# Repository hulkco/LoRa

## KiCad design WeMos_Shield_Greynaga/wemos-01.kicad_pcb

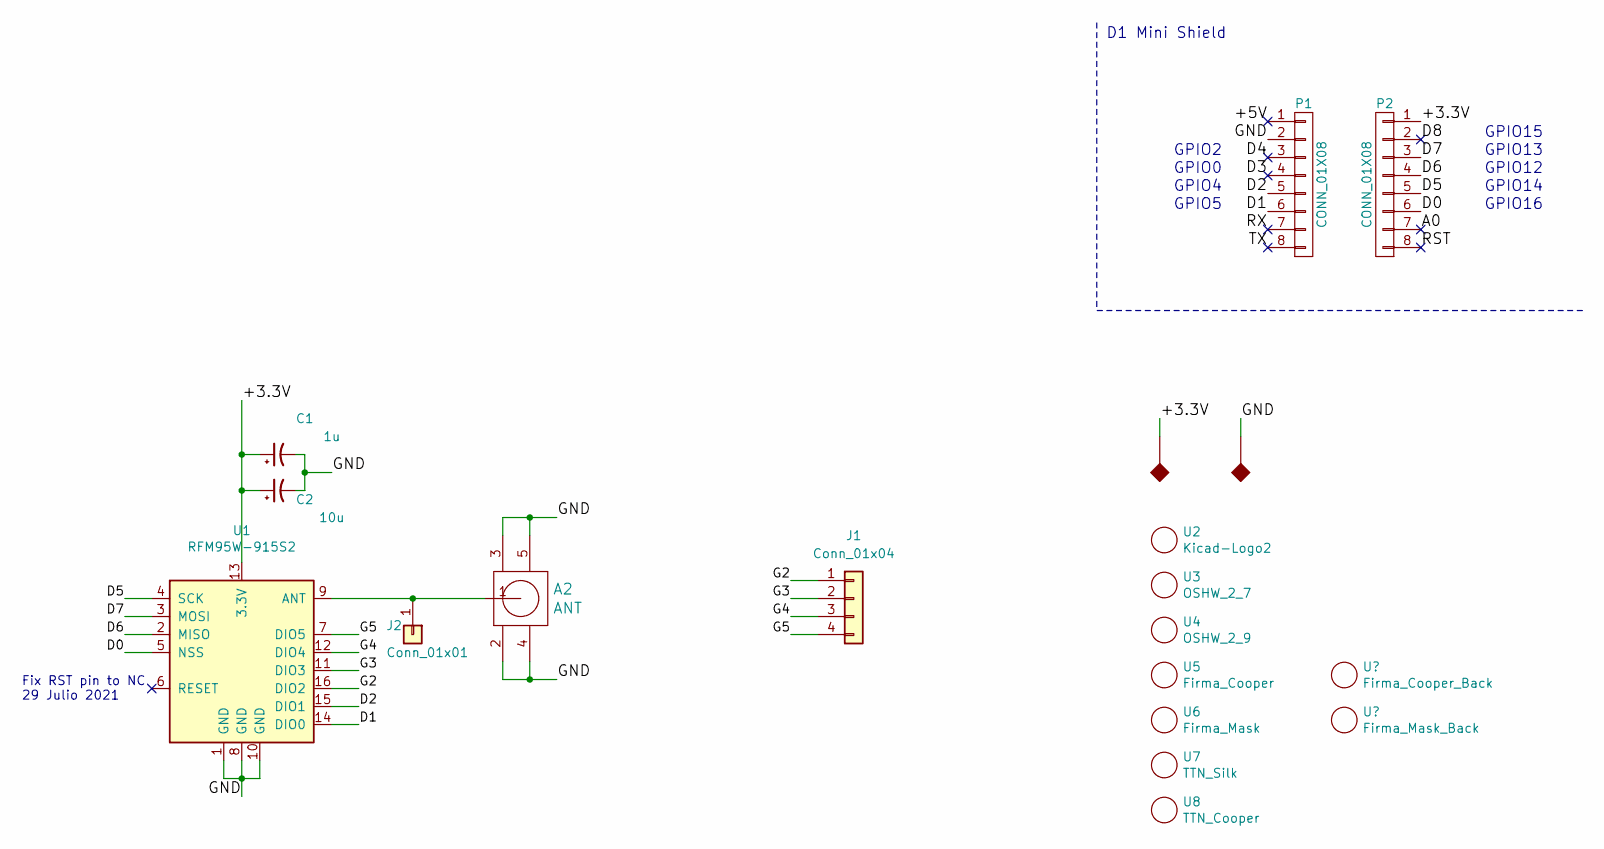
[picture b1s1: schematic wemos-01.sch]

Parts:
A2: ANT; SMA_EDGELAUNCH_UFL_WeMos_Lora
C1: 1u; C_0805_2012Metric_Pad1.29x1.40mm_HandSolder
C2: 10u; C_0805_2012Metric_Pad1.29x1.40mm_HandSolder
J1: Conn_01x04; PinSocket_1x04_P2.54mm_WeMos
J2: Conn_01x01; PinSocket_1x01_P2.54mm_WeMos
P1, P2: CONN_01X08; D1_mini_Pin_Header
U1: RFM95W-915S2; HOPERF_RFM9XW_SMD_WeMos
U2: Kicad-Logo2; KiCad-Logo2_6mm_SilkScreen
U3: OSHW_2_7; OSHW-Logo2_7.3x6mm_SilkScreen
U4: OSHW_2_9; OSHW-Logo2_9.8x8mm_SilkScreen
U5: Firma_Cooper; greynaga6-2-Cooper
U6: Firma_Mask; greynaga6-2-Mask
U7: TTN_Silk; ttn_logo3
U8: TTN_Cooper; ttn_logoCu1

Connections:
/+3.3V: C1.1, C2.1, P2.1, U1.13 (3.3V)
/+5V: P1.1
/A0: P2.7
/D0: P2.6, U1.5 (NSS)
/D1: P1.6, U1.14 (DIO0)
/D2: P1.5, U1.15 (DIO1)
/D3: P1.4
/D4: P1.3
/D5: P2.5, U1.4 (SCK)
/D6: P2.4, U1.2 (MISO)
/D7: P2.3, U1.3 (MOSI)
/D8: P2.2
/G2: J1.1, U1.16 (DIO2)
/G3: J1.2, U1.11 (DIO3)
/G4: J1.3, U1.12 (DIO4)
/G5: J1.4, U1.7 (DIO5)
/GND: A2.2, A2.3, A2.4, A2.5, C1.2, C2.2, P1.2, U1.1 (GND), U1.8 (GND), U1.10 (GND)
/RST: P2.8
/RX: P1.7
/TX: P1.8
unnamed: A2.1, J2.1, U1.9 (ANT)

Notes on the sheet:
GPIO2
GPIO0
GPIO4
GPIO5
GPIO15
GPIO13
GPIO12
GPIO14
GPIO16
D1 Mini Shield
Fix RST pin to NC 29 Julio 2021

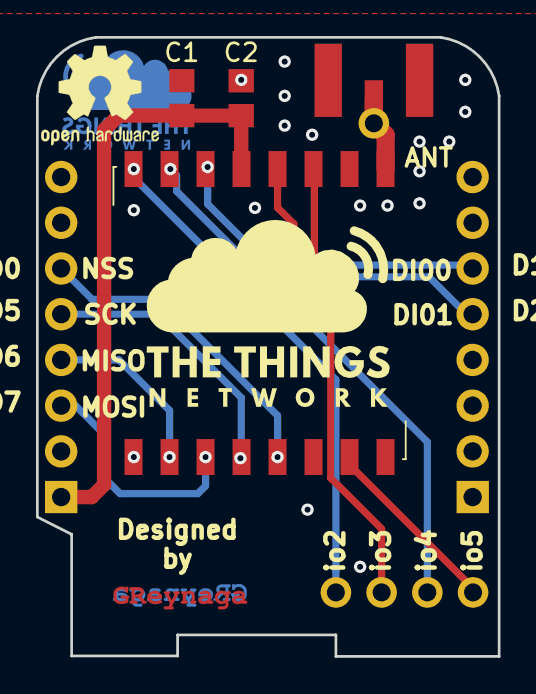
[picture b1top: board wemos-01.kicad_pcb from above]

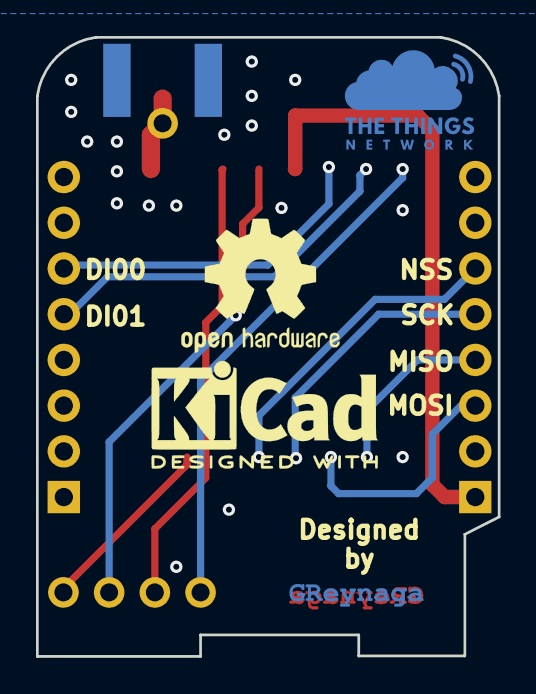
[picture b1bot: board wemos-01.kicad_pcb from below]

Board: 2 copper layers, 25.7 x 34.4 mm, 17 parts (7 on the bottom side), 13 nets.

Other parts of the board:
U5#2: Firma_Cooper; greynaga6-2-Cooper
U6#2: Firma_Mask; greynaga6-2-Mask

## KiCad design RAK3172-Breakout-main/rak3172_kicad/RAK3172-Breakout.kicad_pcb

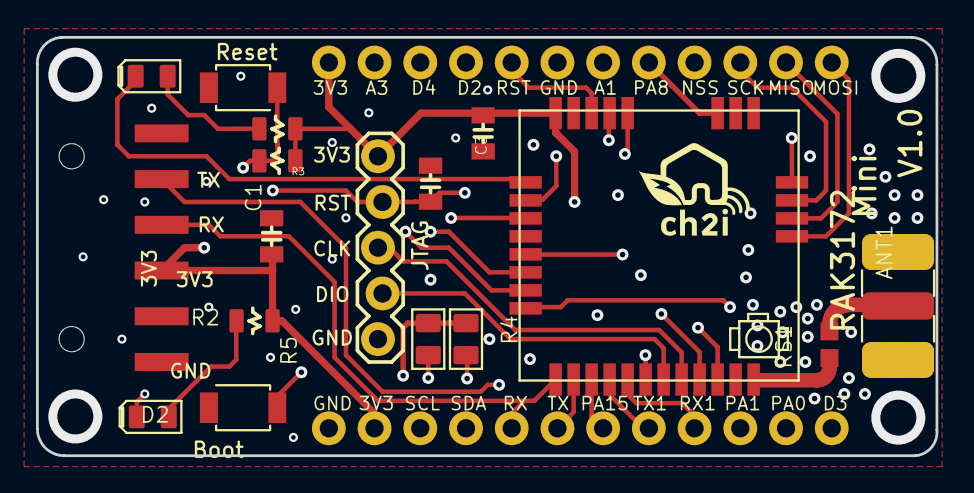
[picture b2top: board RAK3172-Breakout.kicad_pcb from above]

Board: 4 copper layers, 50.0 x 23.2 mm, 26 parts (0 on the bottom side), 31 nets.

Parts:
ANT1: DIP SMA-K; SMA5P-SMD-5.1-6.5X6.5X16.5MM
C1, C4, C5, C6: 10uF; 0805-CAP
C2, C3: 100nF; 0805-CAP
C7: 100uF; 0805-CAP
COIN1: CR2450; CR2450-SMD
D1: GREEN; LED-0805
D2: RED; LED-0805
J1: FTDI; 1X06-SMD_RA_MALE
J2, J4: CONN_12NO_SILK; 1X12_NO_SILK
J3: JTAG; 1X05_LOCK
R1, R2, R3: 1K; 0805-RES
R4, R5: 4K7; R0805
RS1: 0R; 0603-MATCHNET
SW1: RESET; SW2-2.6-3.0X2.5X1.2+0.4MM
SW2: BOOT0; SW2-2.6-3.0X2.5X1.2+0.4MM
U$1, U$2: LOGO_C2I_015
U$3: RAK3172HF; RAK3172

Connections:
3V3: C1.2, C3.2, C4.2, C5.2, C6.2, C7.2, COIN1.+$2, J1.4, J2.2, J3.5, J4.12, R1.2, R2.2, R3.1, R4.1, R5.1, U$3.24
/A1: J4.6, U$3.26
/A3: J4.11, U$3.31
/D2: J4.9, U$3.27
/D3: J2.12, U$3.32
/D4: J4.10, U$3.30
/MISO: J4.2, U$3.14
/MOSI: J4.1, U$3.13
/NSS: J4.4, U$3.16
/PA0: J2.11, U$3.29
/PA1: J2.10, U$3.6
/PA8: J4.5, U$3.19
/PA15: J2.7, U$3.3
/RST: C2.2, J3.4, J4.8, R3.2, SW1.2, U$3.22
/RX1: J2.9, U$3.5
/RX2: J1.3, J2.5, U$3.1
/SCK: J4.3, U$3.15
/SCL: J2.3, R5.2, U$3.9
/SDA: J2.4, R4.2, U$3.10
/SWCLK: J3.3, U$3.8
/SWDIO: J3.2, U$3.7
/TX1: J2.8, U$3.4
/TX2: J1.2, J2.6, U$3.2
GND: ANT1.GND1, ANT1.GND2, ANT1.GND3, ANT1.GND4, C1.1, C2.1, C3.1, C4.1, C5.1, C6.1, C7.1, COIN1.-, J1.6, J2.1, J3.1, J4.7, SW1.1, SW2.2, U$3.11, U$3.17, U$3.18, U$3.23, U$3.28
unnamed: ANT1.ANT, RS1.2
unnamed: D1.+, R1.1
unnamed: D1.-, U$3.25
unnamed: D2.+, R2.1
unnamed: D2.-, U$3.20
unnamed: RS1.1, U$3.12
unnamed: SW2.1, U$3.21

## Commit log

2018-06-29 Add Wemos Shield
2018-06-29 Add Bricolabs Shield
2018-06-29 Add some updates
2018-11-26 Add images PCBs
2021-04-08 Add gitignore
2021-04-08 update gitignore
